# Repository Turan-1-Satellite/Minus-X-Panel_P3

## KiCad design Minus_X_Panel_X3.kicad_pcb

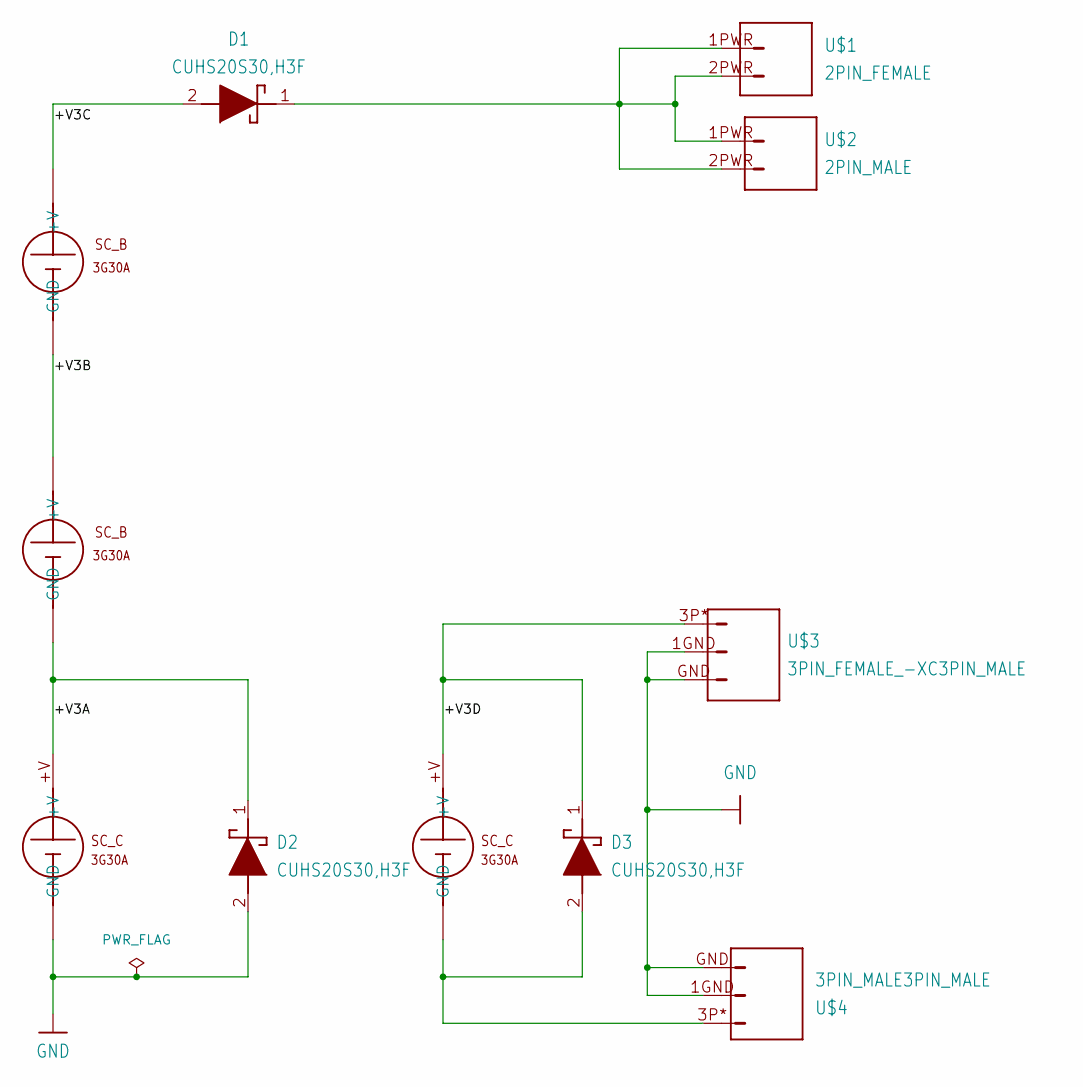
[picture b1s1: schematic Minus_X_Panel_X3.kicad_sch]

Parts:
D1, D2, D3: CUHS20S30,H3F
S1, S3: solar_cell_B
S2, S4: Solar_cell_C; solar_cell_C
U$1: 2PIN_FEMALE; FSR-41057-02-F
U$2: 2PIN_MALE; PSR-410253-02-M
U$3: 3PIN_FEMALE_-XC3PIN_MALE; FSR-41057-03-F
U$4: 3PIN_MALE3PIN_MALE; PSR-410253-03-M

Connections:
/+V3A: D2.1 (K), S2.+V, S3.GND
/+V3B: S1.GND, S3.+V
/+V3C: D1.2 (A), S1.+V
/+V3D: D3.1 (K), S4.+V, U$3.3P*
GND: D2.2 (A), S2.GND, U$3.1GND, U$3.GND, U$4.1GND, U$4.GND
unnamed: D1.1 (K), U$1.1PWR, U$1.2PWR, U$2.1PWR, U$2.2PWR
unnamed: D3.2 (A), S4.GND, U$4.3P*

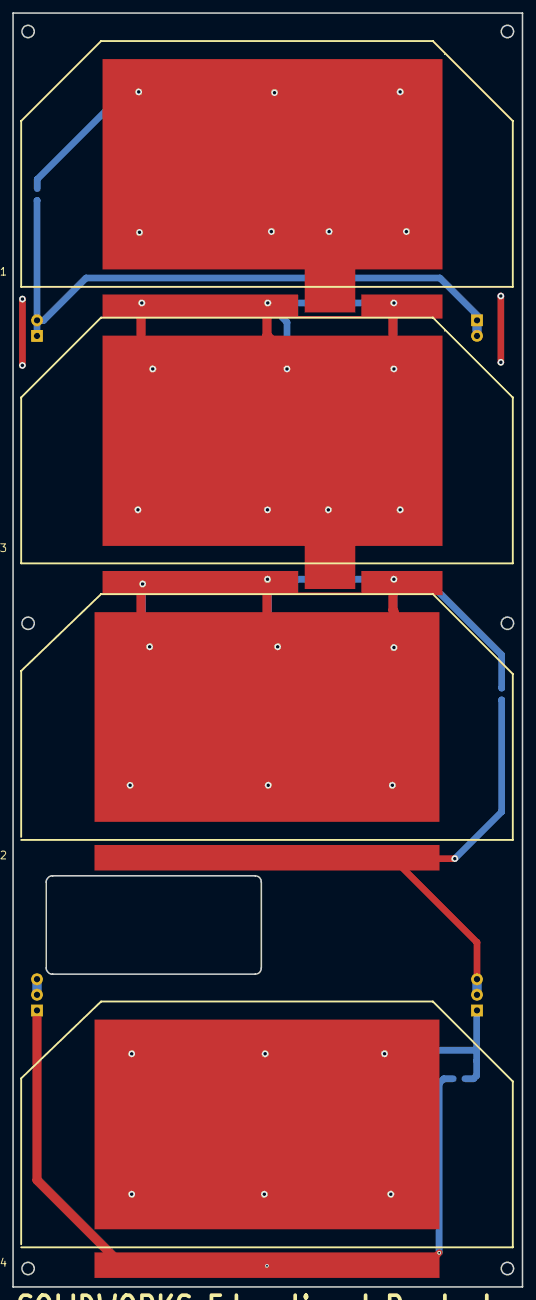
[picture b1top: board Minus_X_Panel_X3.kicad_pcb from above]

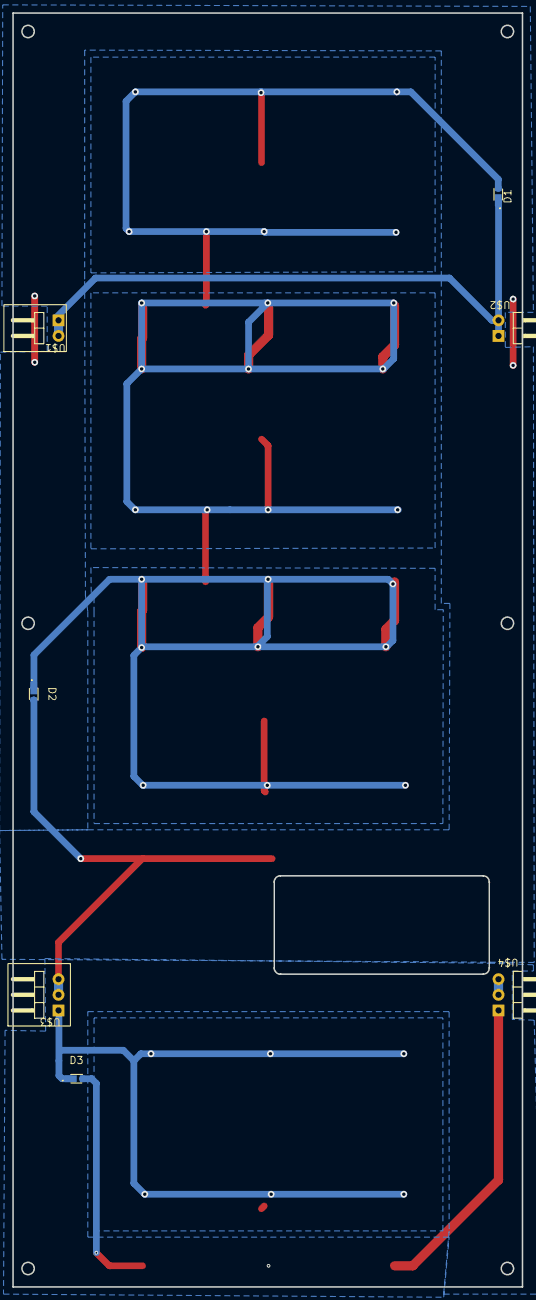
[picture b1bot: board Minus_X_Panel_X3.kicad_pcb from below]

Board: 2 copper layers, 82.9 x 207.3 mm, 11 parts (7 on the bottom side), 7 nets.

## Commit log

2026-03-25 footprint of the Panel is modified with tracking
2026-04-13 Updated the Pin Configuration
